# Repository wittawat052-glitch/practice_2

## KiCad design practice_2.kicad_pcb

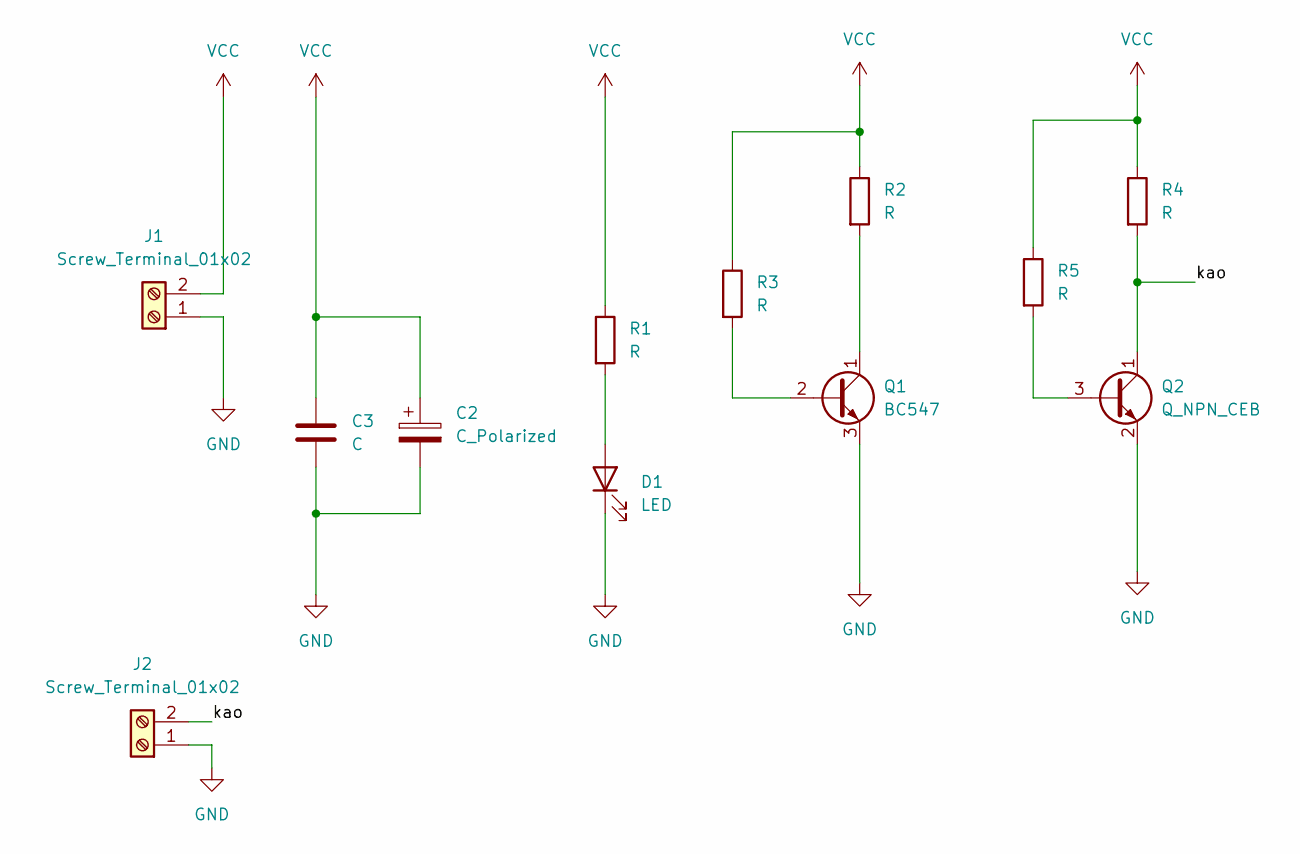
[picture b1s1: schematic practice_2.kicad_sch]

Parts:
C2: C_Polarized; CP_Radial_D10.0mm_P5.00mm
C3: C; C_Radial_D10.0mm_H12.5mm_P5.00mm
D1: LED; LED_D3.0mm
J1, J2: Screw_Terminal_01x02; TerminalBlock_MaiXu_MX126-5.0-02P_1x02_P5.00mm
Q1: BC547; TO-92_Inline
Q2: Q_NPN_CEB; TO-92L_Inline_Wide
R1, R2, R3, R4, R5: R; R_Axial_DIN0309_L9.0mm_D3.2mm_P12.70mm_Horizontal

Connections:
/kao: J2.2, Q2.1 (C), R4.2
GND: C2.2, C3.2, D1.1 (K), J1.1, J2.1, Q1.3 (E), Q2.2 (E)
unnamed: D1.2 (A), R1.2
unnamed: Q1.2 (B), R3.2
unnamed: Q1.1 (C), R2.2
unnamed: Q2.3 (B), R5.2
VCC: C2.1, C3.1, J1.2, R1.1, R2.1, R3.1, R4.1, R5.1

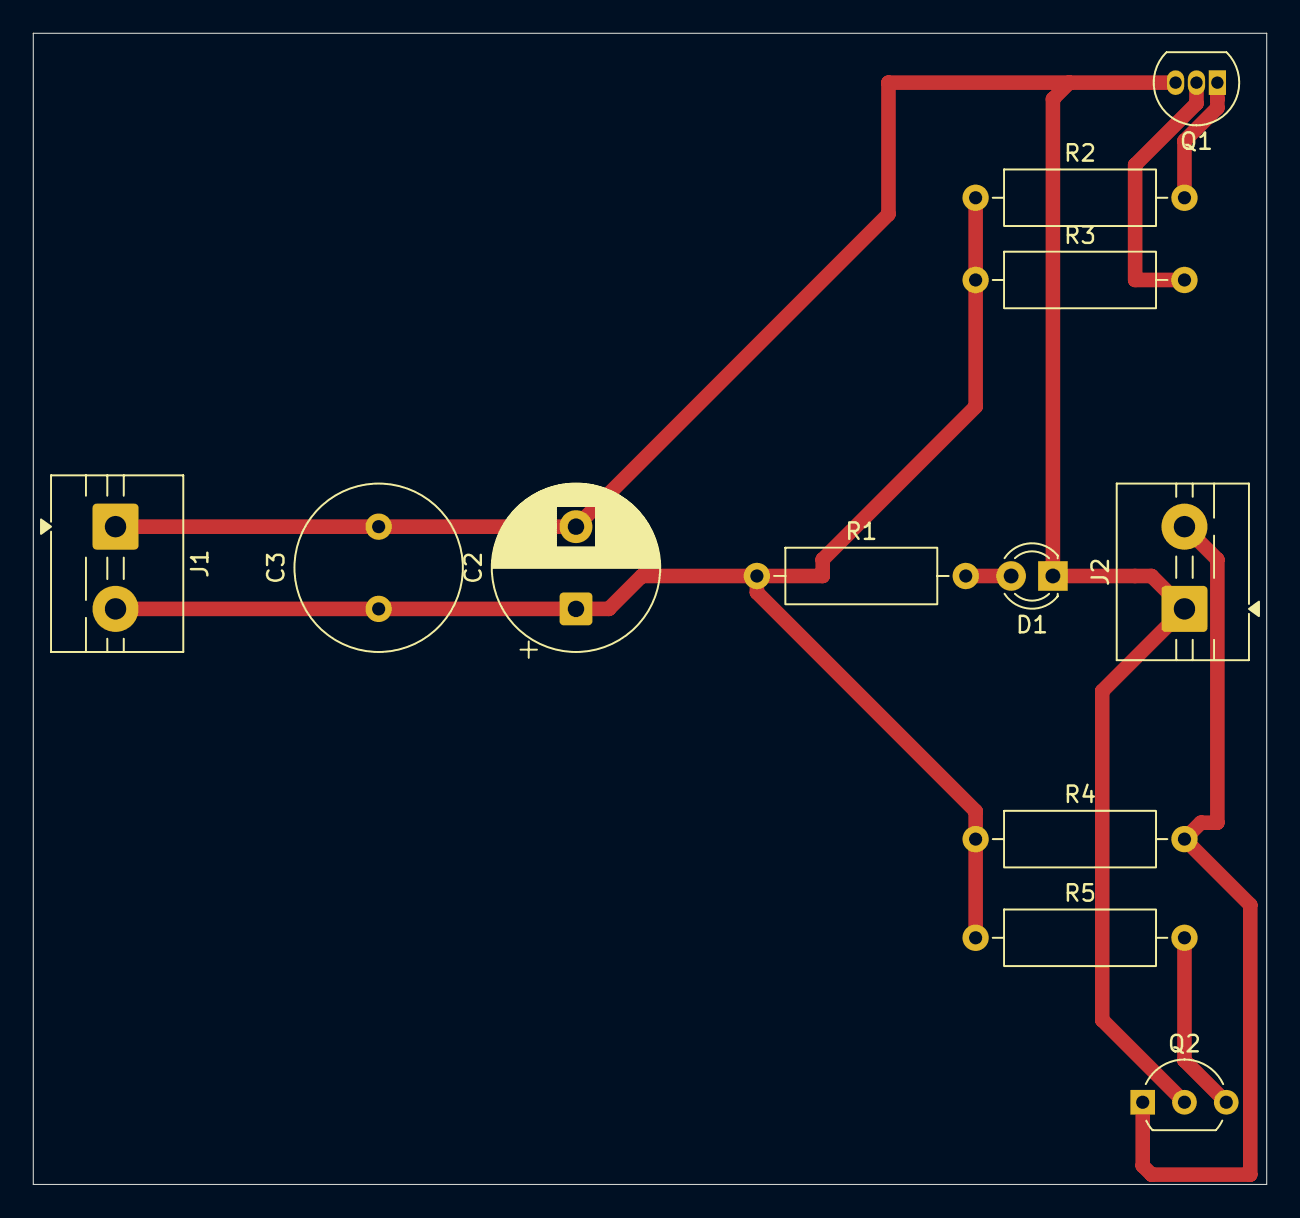
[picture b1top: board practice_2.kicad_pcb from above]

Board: 2 copper layers, 75.0 x 70.0 mm, 12 parts (0 on the bottom side), 7 nets.
